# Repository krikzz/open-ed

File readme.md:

# Open-ED

Open-ED is a very simple and cheap open source Genesis/Megadrive cartridge.
The cartridge does not have its own processor or FPGA, 
it is built in the old school style using only memory and discrete logic. 
Cartridge design uses an absolute minimum of inexpensive components.

Supported mappers:<br/>
ROM_4M		Most games work in this mode<br/>
ROM_2M+RAM	Some games with battery ram<br/>
ROM_4M+RAM	Beyond Oasis, Sonic-3 etc<br/>

Content description:<br/>
fabrication: pcb gerber files, bill of materials, menu binary<br/>
menu:	menu sources<br/>
pcb_src: pcb sources<br/>
schematic: cartridge schematics<br/>
flashkit-md.exe: flaskit software v1.0.0.1<br/>
open-ed.v: cartridge design in verilog<br/>
open-ed-mapper: cartridge mapper description<br/>
flashkit_mod.jpg: FlashKit mod required for open-ed programming<br/>
open-ed.jpg: cartridge photo<br/>

Menu programming<br/>
open-ed.md should be burned to the upper bank of flash memory (0x400000-0x40FFFF)<br/>
Menu can be programmed to the flash chip using any flash programmer or FlashKit<br/>
FlashKit can program menu onboard (flashkit-md v1.0.0.1 required)<br/>
FlashKit have to be modified: 10k pullup to the cart pin B27(/VRES)<br/>

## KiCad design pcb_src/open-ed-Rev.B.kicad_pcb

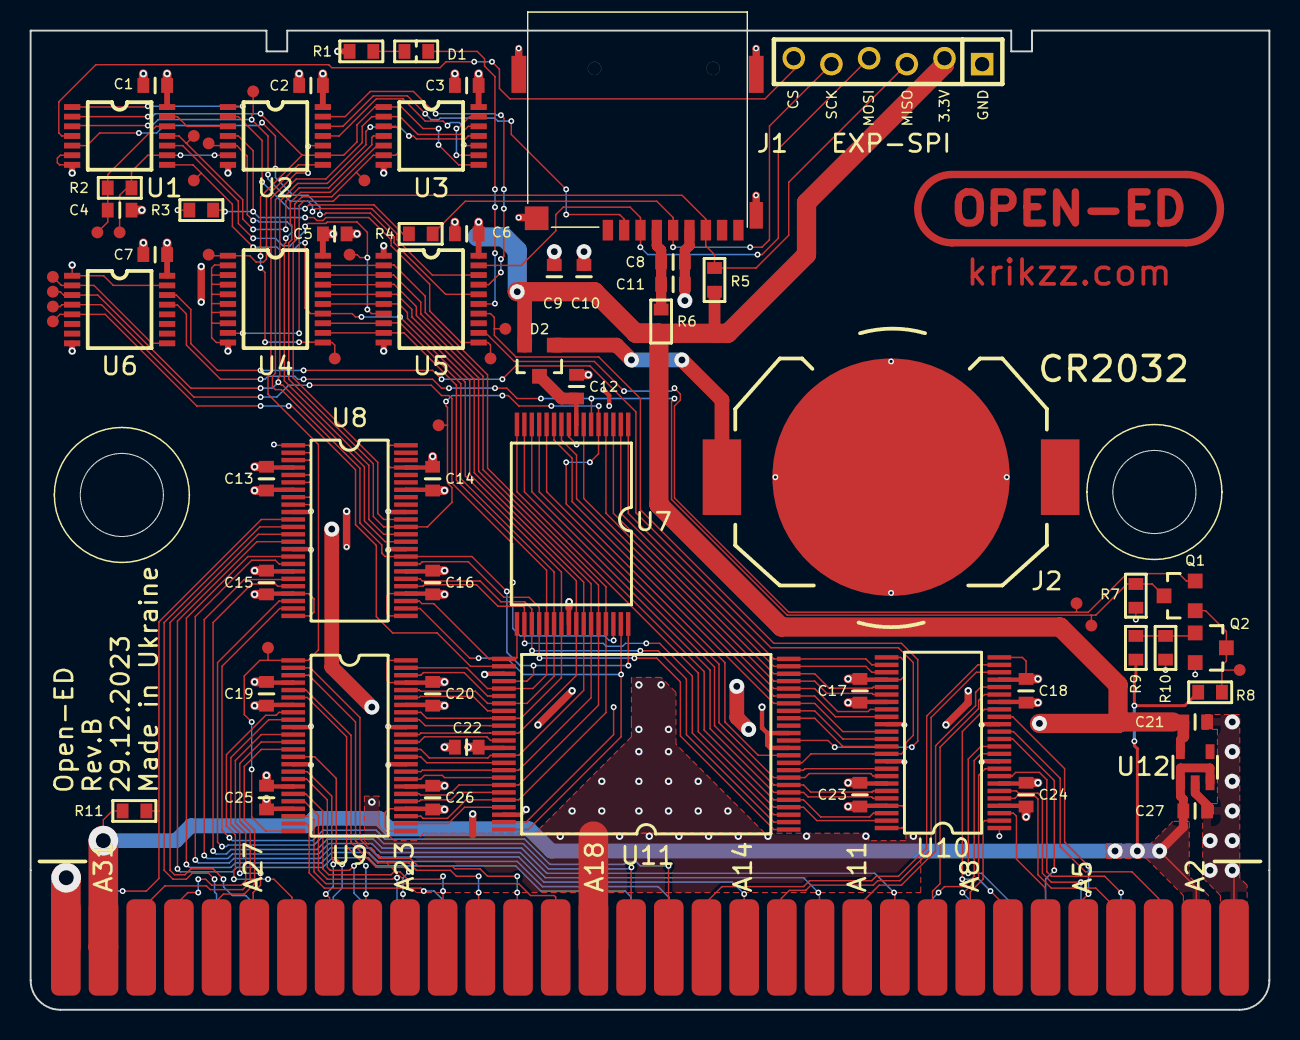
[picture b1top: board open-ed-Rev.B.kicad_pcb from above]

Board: 2 copper layers, 83.5 x 66.0 mm, 59 parts (1 on the bottom side), 121 nets.

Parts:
C1, C2, C3, C5, C6, C7, C8, C12, C13, C14, C15, C16, C17, C18, C19, C20, C22, C23, C24, C25, C26: 0.1u GCJ188R71H104KA12D; SMD0603C_1
C4: 100p GCM1885C2A101JA16D; SMD0603C_1
C9, C10: 22u GRT188R61A226ME13D; SMD0603C_1
C11, C21, C27: 4.7u GRT188C71C475KE13D; SMD0603C_1
D1: RED SML-D12U8WT86; SMD0603L_1
D2: BAT54C,215; SMD_TRANS_1
J1: Olimex MICRO-SD-CARD; SD_MINI2_1
J2: BAT-HLD-001; CR2032_THT_1
J3: x; JTAG-ROW_1
Q1: SI2307CDS-T1-E3; MOSFET_SMD_1
Q2: MMBT2222ALT1G; T_MMBT2222_1
R1, R3, R10: 1K AC0603FR-101KL; SMD0603R_1
R2: 470r AC0603FR-07470RL; SMD0603R_1
R4: 33r AC0603FR-0733RL; SMD0603R_1
R5, R7, R8, R11: 4.7k AC0603FR-074K7L; SMD0603R_1
R6: 0r AC0603FR-070RL; SMD0603R_1
R9: 6.2K AC0603FR-076K2L; SMD0603R_1
SEGA1: x; SEGA_CART_TOP_1
SEGA2: x; SEGA_CART_BOT_1
U1, U3: SN74HC02PWR; 74HC02_TSSOP_1
U2: SN74HC04PWR; 74HC04_TSSOP_1
U4, U5: SN74HC574PWR; 74HC573_TSSOP_1
U6: SN74HC139PWR; 74HC139_TSSOP_1
U7: IS62WV1288BLL-55HLI; TS0P32_1
U8, U9, U10: 74LVC162245ADGG; SN74LVTH162245D_1
U11: M29W064FB70N3E; M29W640_1
U12: 3.3v MCP1824T-3302E/OT; MCP1824_1

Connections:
A1: U7.a3, U8.2a7, U11.A1
A2: U7.a11, U10.2a8, U11.A2
A3: U7.a9, U10.2a7, U11.A3
A4: U7.a8, U10.2a6, U11.A4
A5: U7.a13, U10.2a5, U11.A5
A6: U7.a15, U10.2a4, U11.A6
A7: U7.a16, U10.2a3, U11.A7
A8: U7.a14, U10.2a2, U11.A8
A9: U7.a12, U10.1a5, U11.A9
A10: U7.a7, U10.1a4, U11.A10
A11: U7.a6, U10.1a3, U11.A11
A12: U7.a5, U10.1a2, U11.A12
A13: U7.a4, U10.1a1, U11.A13
A14: U7.a2, U8.2a6, U11.A14
A15: U7.a1, U8.2a5, U11.A15
A16: U7.a0, U8.2a4, U11.A16
A17: U7.a10, U8.2a8, U11.A17
A18: U10.2a1, U11.A18
A19: U10.1a8, U11.A19
A20: U10.1a6, U11.A20
A21: U6.2a0, U10.1a7, U11.A21
BUS_DIR: U2.5y, U9.1dir, U9.2dir
BUS_OE_N: U2.5a, U3.3y
CART_OE: U3.3b, U3.4y
CE_LO_N: U3.4a, U6.1a1, U8.2a2
CPU_D2_RST: U1.3y, U5.d5
D0: U4.q7, U5.d7, U7.d0, U9.1a1, U11.D0
D1: U4.q6, U5.d6, U7.d1, U9.1a3, U11.D1
D2: U1.3a, U4.q5, U7.d2, U9.1a5, U11.D2
D3: U4.q4, U5.d4, U7.d3, U9.1a7, U11.D3
D4: U4.q3, U5.d3, U7.d4, U9.2a1, U11.D4
D5: U4.q2, U5.d2, U7.d5, U9.2a3, U11.D5
D6: U4.q1, U5.d1, U7.d6, U9.2a5, U11.D6
D7: U4.q0, U5.d0, U7.d7, U9.2a7, U11.D7
D8: SEGA2.d8, U9.1b2
D9: U9.1a4, U11.D9
D10: U9.1a6, U11.D10
D11: U9.1a8, U11.D11
D12: U9.2a2, U11.D12
D13: U9.2a4, U11.D13
D14: U9.2a6, U11.D14
D15: U9.2a8, U11.D15A0
EXP_SS: U1.2a, U5.q3
EXP_SS_N: J3.gnd, U1.2y
GND: C1.1, C2.1, C3.1, C4.1, C5.2, C6.1, C7.1, C8.1, C9.1, C10.1, C11.1, C12.1, C13.2, C14.2, C15.1, C16.1, C17.2, C18.2, C19.2, C20.2, C21.2, C22.1, C23.1, C24.1, C25.1, C26.1, C27.2, J1.10, J1.11, J1.14, J1.15, J1.gnd, J2.3, J3.tdo, Q2.2e, R1.1, R3.2, R7.2, R10.1, SEGA1.cart, SEGA2.gnd1, SEGA2.gnd2, SEGA2.gnd3, U1.2b, U1.gnd, U2.gnd, U3.gnd, U4.d0, U4.d1, U4.d2, U4.d3, U4.d4, U4.d5, U4.d6, U4.gnd, U5.gnd, U5.oe, U6.1e, U6.2e, U6.gnd, U7.gnd, U7.nc, U8.1b1, U8.1b2, U8.1b3, U8.1b4, U8.1b5, U8.1b6, U8.1dir, U8.2dir, U8.gnd1, U8.gnd2, U8.gnd3, U8.gnd4, U8.gnd5, U8.gnd6, U8.gnd7, U8.gnd8, U8.~1oe, U8.~2oe, U9.gnd1, U9.gnd2, U9.gnd3, U9.gnd4, U9.gnd5, U9.gnd6, U9.gnd7, U9.gnd8, U9.~1oe, U9.~2oe, U10.1dir, U10.2dir, U10.gnd1, U10.gnd2, U10.gnd3, U10.gnd4, U10.gnd5, U10.gnd6, U10.gnd7, U10.gnd8, U10.~1oe, U10.~2oe, U11.GND, U11.GND1, U12.gnd
LED: D1.2, U5.q4
MD_A1: SEGA2.a0, U8.2b7
MD_A2: SEGA2.a1, U10.2b8
MD_A3: SEGA2.a2, U10.2b7
MD_A4: SEGA2.a3, U10.2b6
MD_A5: SEGA2.a4, U10.2b5
MD_A6: SEGA2.a5, U10.2b4
MD_A7: SEGA2.a6, U10.2b3
MD_A8: SEGA2.a7, U10.2b2
MD_A9: SEGA1.a8, U10.1b5
MD_A10: SEGA1.a9, U10.1b4
MD_A11: SEGA2.a10, U10.1b3
MD_A12: SEGA2.a11, U10.1b2
MD_A13: SEGA2.a12, U10.1b1
MD_A14: SEGA2.a13, U8.2b6
MD_A15: SEGA2.a14, U8.2b5
MD_A16: SEGA2.a15, U8.2b4
MD_A17: SEGA2.a16, U8.2b8
MD_A18: SEGA1.a17, U10.2b1
MD_A19: SEGA1.a18, U10.1b8
MD_A20: SEGA1.a19, U10.1b6
MD_A21: SEGA1.a20, U10.1b7
MD_CE_LO_N: SEGA1.~ce_l, U8.2b2
MD_D0: SEGA2.d0, U9.1b1
MD_D1: SEGA2.d1, U9.1b3
MD_D2: SEGA2.d2, U9.1b5
MD_D3: SEGA2.d3, U9.1b7
MD_D4: SEGA2.d4, U9.2b1
MD_D5: SEGA2.d5, U9.2b3
MD_D6: SEGA2.d6, U9.2b5
MD_D7: SEGA2.d7, U9.2b7
MD_D8: U9.1a2, U11.D8
MD_D9: SEGA2.d9, U9.1b4
MD_D10: SEGA2.d10, U9.1b6
MD_D11: SEGA2.d11, U9.1b8
MD_D12: SEGA1.d12, U9.2b2
MD_D13: SEGA1.d13, U9.2b4
MD_D14: SEGA1.d14, U9.2b6
MD_D15: SEGA1.d15, U9.2b8
MD_OE_N: SEGA1.~oe, U8.2b3
MD_RST_N: SEGA1.~rst, U8.2b1
MD_TIME_N: R11.2, SEGA1.time, U8.1b7
MD_WE_LO_N: SEGA1.~wel, U8.1b8
NET00001: D1.1, R1.2
NET00010: Q2.1b, R9.2, R10.2
OE_N: U3.1a, U3.4b, U7.oe, U8.2a3, U11.OE
RAM_CE_N: U6.1s0, U7.nce
RAM_ON: Q1.2_s, U5.q7
RAM_ON_N: U6.1a0, U6.2s3
RAM_ON_VST: Q1.3_d, R7.1, U6.2a1, U7.ce2
REG_OE: U1.1a, U2.4a, U3.1y, U3.3a, U4.le
REG_OE_N: U2.4y, U4.oe
REG_SET: R3.1, U2.2y, U5.le
REG_SET_N: U1.4y, U2.2a
REG_WE: U1.4a, U3.2y
ROM_BANK: U5.q5, U11.A22
ROM_CE_N: U6.1s1, U11.CE
RST_I: R2.1, U1.3b, U2.3y
RST_ID: C4.2, R2.2, U1.4b
RST_N: U2.3a, U8.2a1
SDC_SS: U2.6a, U5.q2
SDC_SS_N: J1.ss, U2.6y
SPI_CK: U1.1b, U5.q1
SPI_MISO: J1.miso, J3.tck, R5.2, U4.d7
SPI_MOSI: J1.mosi, J3.tdi, U5.q0
SPI_SCK: R4.1, U2.1y
SPI_SCK_I: U1.1y, U2.1a
SPI_SCK_R: J1.clk, J3.tms, R4.2
TIME_N: U3.1b, U3.2b, U8.1a7
VBAT: D2.3, J2.2
VCC3: C1.2, C2.2, C3.2, C5.1, C6.2, C7.2, C9.2, C10.2, C13.1, C14.1, C15.2, C16.2, C17.1, C18.1, C19.1, C20.1, C21.1, C22.2, C23.2, C24.2, C25.2, C26.2, D2.2, J3.vcc, R5.1, R6.1, U1.vcc, U2.vcc, U3.vcc, U4.vcc, U5.vcc, U6.vcc, U8.vcc1, U8.vcc2, U8.vcc3, U8.vcc4, U9.vcc1, U9.vcc2, U9.vcc3, U9.vcc4, U10.vcc1, U10.vcc2, U10.vcc3, U10.vcc4, U11.BYTE, U11.RST, U11.VCC, U11.WP, U12.vout
VCC5: C27.1, R8.2, R9.1, R11.1, SEGA2.vcc1, SEGA2.vcc2, U12.shdn, U12.vin
VCC_RAM: C12.2, D2.1, U7.vcc
VCC_SD: C8.2, C11.2, J1.vcc, R6.2
VCC_STB_N: Q1.1_g, Q2.3c, R8.1
WE_LO_N: U3.2a, U7.we, U8.1a8, U11.WE

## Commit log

2024-06-11 init
2024-06-11 cart photo
2024-06-16 Update Readme to Markdown and embed image.
2024-06-18 boxart
